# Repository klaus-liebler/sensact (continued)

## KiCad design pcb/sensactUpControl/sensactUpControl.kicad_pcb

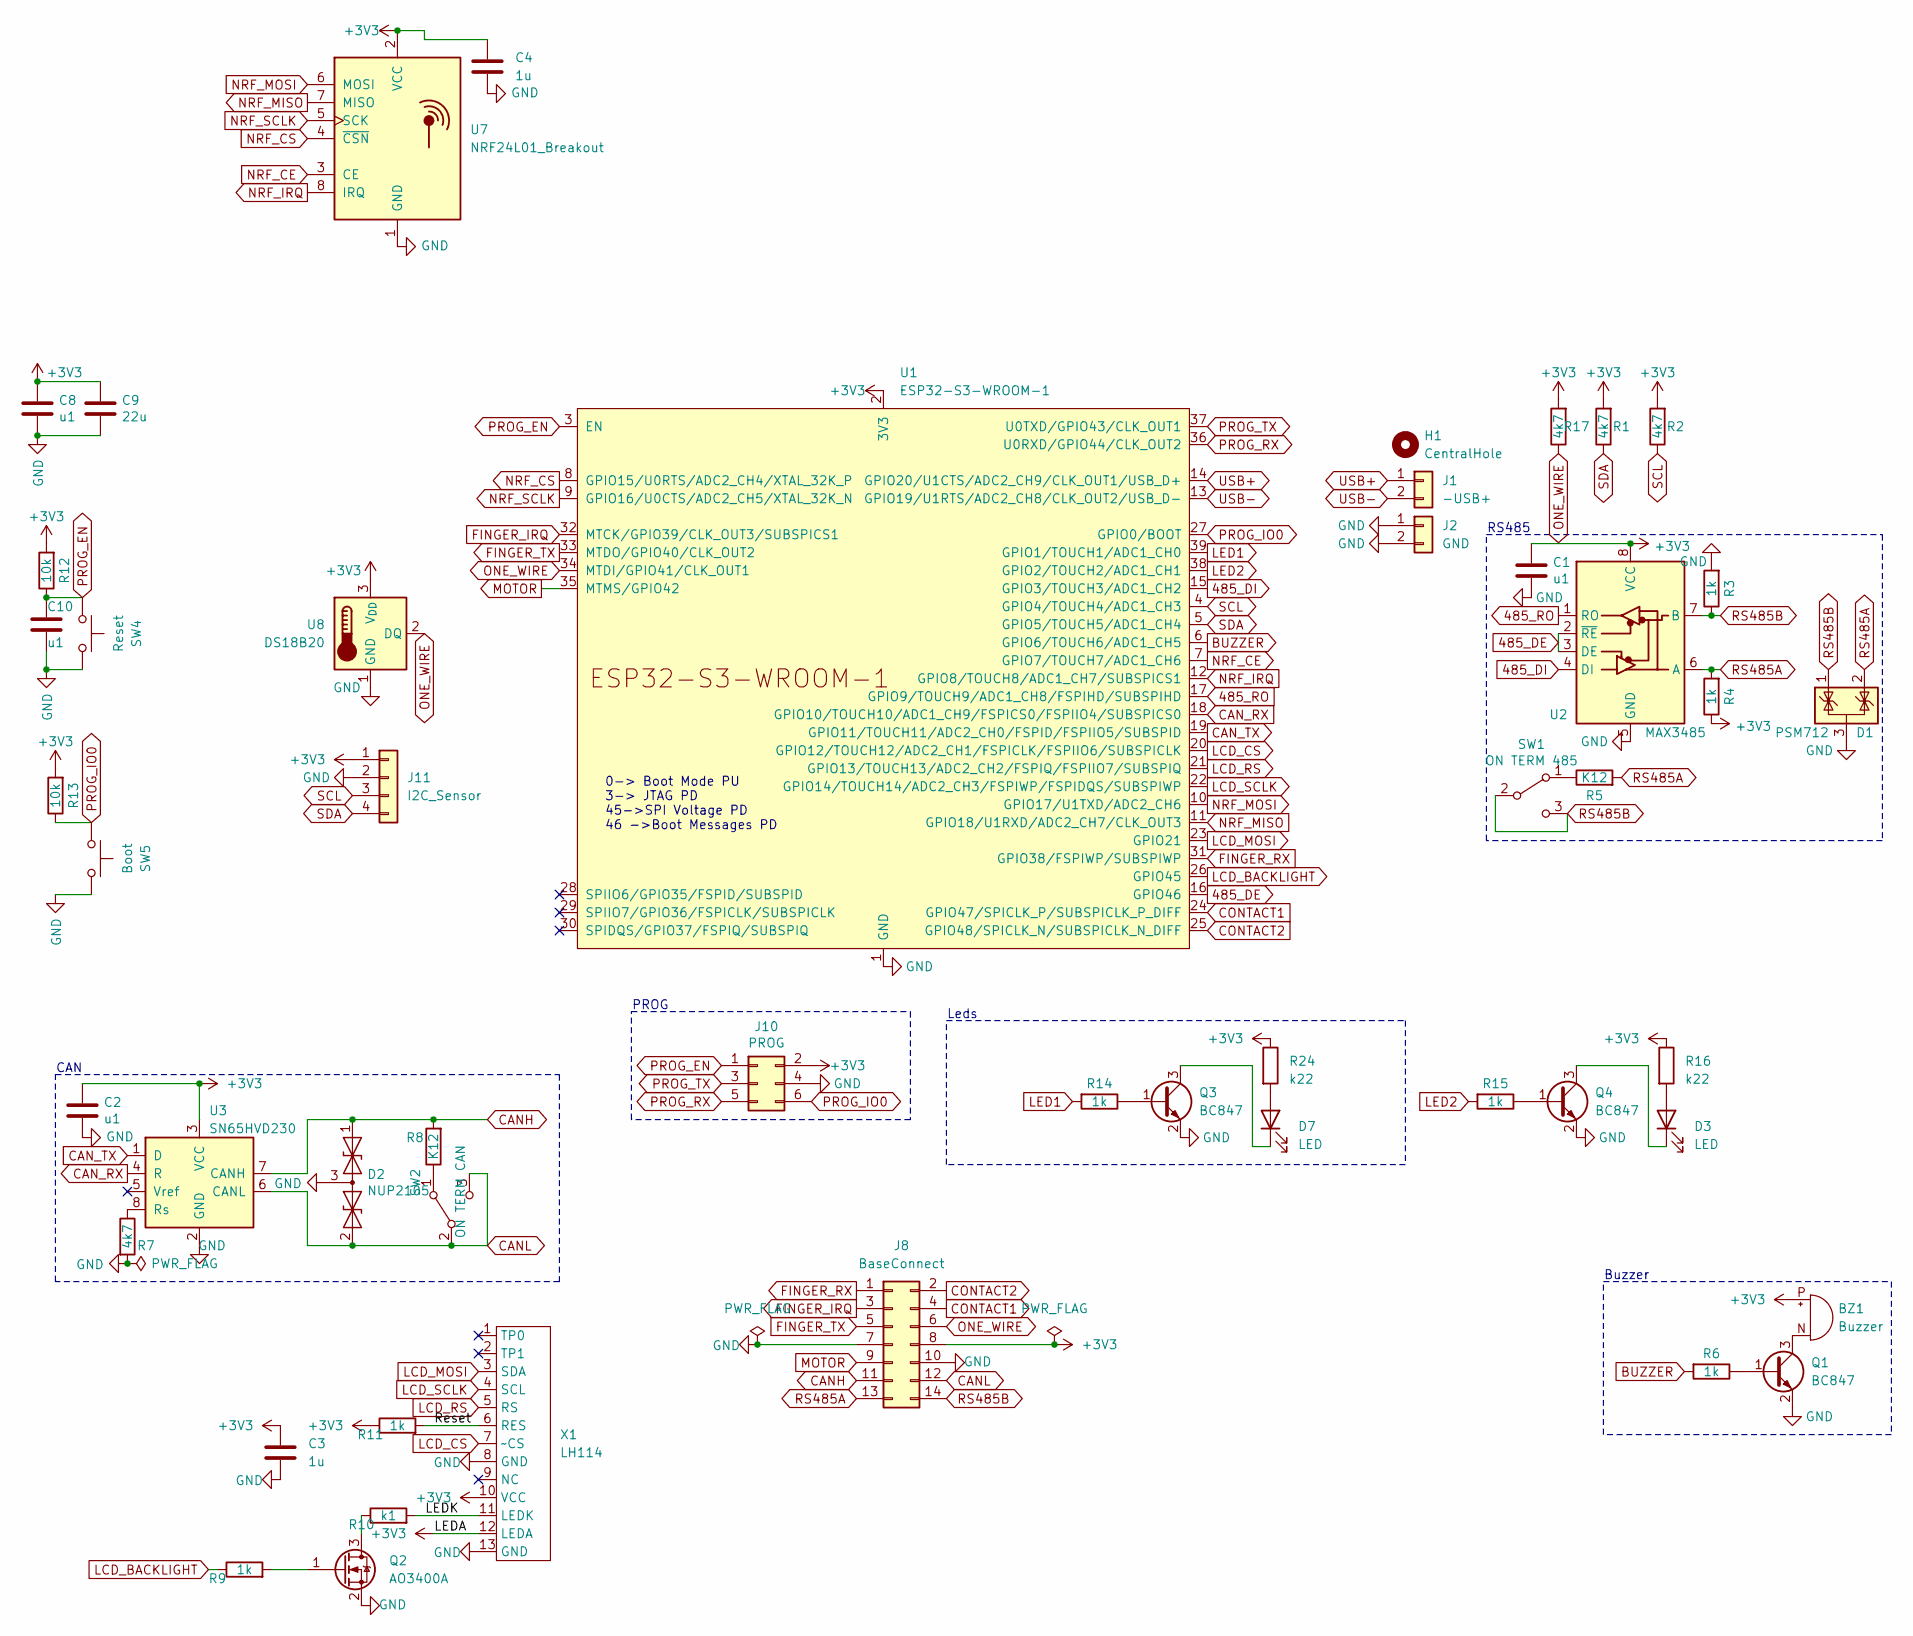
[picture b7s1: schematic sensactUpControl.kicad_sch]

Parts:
BZ1: Buzzer; XDCR_CMT-7525-80-SMT-TR_handsolder
C1, C2, C8, C10: u1; C_0805_2012Metric_Pad1.18x1.45mm_HandSolder
C3, C4: 1u; C_0805_2012Metric_Pad1.18x1.45mm_HandSolder
C9: 22u; C_0805_2012Metric_Pad1.18x1.45mm_HandSolder
D1: PSM712; SOT-23_Handsoldering
D2: NUP2105; SOT-23_Handsoldering
D3, D7: LED; LED_PLCC_2835_Handsoldering
H1: CentralHole; MountingHole_3.2mm_M3
J1: -USB+; PinHeader_1x02_P2.00mm_Vertical
J2: GND; PinHeader_1x02_P2.00mm_Vertical
J8: BaseConnect; PinHeader_2x07_P2.54mm_Vertical
J10: PROG; IDC_2x03_P1.27mm_Vertical
J11: I2C_Sensor; PinHeader_1x04_P2.54mm_Vertical
Q1, Q3, Q4: BC847; SOT-23_Handsoldering
Q2: AO3400A; SOT-23_Handsoldering
R1, R2, R7, R17: 4k7; R_0805_2012Metric_Pad1.20x1.40mm_HandSolder
R3, R4, R6, R9, R11, R14, R15: 1k; R_0805_2012Metric_Pad1.20x1.40mm_HandSolder
R5, R8: K12; R_1206_3216Metric_Pad1.30x1.75mm_HandSolder
R10: k1; R_0805_2012Metric_Pad1.20x1.40mm_HandSolder
R12, R13: 10k; R_0805_2012Metric_Pad1.20x1.40mm_HandSolder
R16, R24: k22; R_1206_3216Metric_Pad1.30x1.75mm_HandSolder
SW1: ON TERM 485; SW_SPDT_PCM12_handsolder
SW2: ON TERM CAN; SW_SPDT_PCM12_handsolder
SW4: Reset; SW_SPST_TL3342_smaller_handsolder
SW5: Boot; SW_SPST_TL3342_smaller_handsolder
U1: ESP32-S3-WROOM-1; ESP32-S3-WROOM-1_handsolder
U2: MAX3485; SOIC-8_3.9x4.9mm_Pitch1.27mm_handsolder
U3: SN65HVD230; SOIC-8_3.9x4.9mm_Pitch1.27mm_handsolder
U7: NRF24L01_Breakout; nRF24L01_Breakout
U8: DS18B20; TO-92_HandSolder
X1: LH114; FP-114 13pol top only

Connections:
485_DE: U1.16 (GPIO46), U2.2 (~RE), U2.3 (DE)
485_DI: U1.15 (GPIO3/TOUCH3/ADC1_CH2), U2.4 (DI)
485_RO: U1.17 (GPIO9/TOUCH9/ADC1_CH8/FSPIHD/SUBSPIHD), U2.1 (RO)
+3V3: BZ1.P (+), C1.2, C2.1, C3.1, C4.1, C8.1, C9.1, J8.8, J10.2, J11.1, R1.2, R2.2, R4.1, R11.1, R12.2, R13.2, R16.1, R17.2, R24.1, U1.2 (3V3), U2.8 (VCC), U3.3 (VCC), U7.2 (VCC), U8.3 (V_{DD}), X1.10 (VCC), X1.12 (LEDA)
/LEDK: R10.2, X1.11 (LEDK)
/Reset: R11.2, X1.6 (RES)
BUZZER: R6.2, U1.6 (GPIO6/TOUCH6/ADC1_CH5)
CANH: D2.1 (A1), J8.11, R8.2, U3.7 (CANH)
CANL: D2.2 (A2), J8.12, SW2.2 (B), SW2.3 (C), U3.6 (CANL)
CAN_RX: U1.18 (GPIO10/TOUCH10/ADC1_CH9/FSPICS0/FSPIIO4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), U3.4 (R)
CAN_TX: U1.19 (GPIO11/TOUCH11/ADC2_CH0/FSPID/FSPIIO5/S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), U3.1 (D)
CONTACT1: J8.4, U1.24 (GPIO47/SPICLK_P/SUBSPICLK_P_DIFF)
CONTACT2: J8.2, U1.25 (GPIO48/SPICLK_N/SUBSPICLK_N_DIFF)
FINGER_IRQ: J8.3, U1.32 (MTCK/GPIO39/CLK_OUT3/SUBSPICS1)
FINGER_RX: J8.1, U1.31 (GPIO38/FSPIWP/SUBSPIWP)
FINGER_TX: J8.5, U1.33 (MTDO/GPIO40/CLK_OUT2)
GND: C1.1, C2.2, C3.2, C4.2, C8.2, C9.2, C10.2, D1.3 (A), D2.3 (common), J2.1, J2.2, J8.7, J8.10, J10.4, J11.2, Q1.2 (E), Q2.2 (S), Q3.2 (E), Q4.2 (E), R3.2, R7.2, SW4.1, SW5.1, U1.1 (GND), U1.40 (GND), U1.41 (GND), U2.5 (GND), U3.2 (GND), U7.1 (GND), U8.1 (GND), X1.8 (GND), X1.13 (GND)
LCD_BACKLIGHT: R9.1, U1.26 (GPIO45)
LCD_CS: U1.20 (GPIO12/TOUCH12/ADC2_CH1/FSPICLK/FSPIIO6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), X1.7 (~CS)
LCD_MOSI: U1.23 (GPIO21), X1.3 (SDA)
LCD_RS: U1.21 (GPIO13/TOUCH13/ADC2_CH2/FSPIQ/FSPIIO7/S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), X1.5 (RS)
LCD_SCLK: U1.22 (GPIO14/TOUCH14/ADC2_CH3/FSPIWP/FSPIDQS/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), X1.4 (SCL)
LED1: R14.2, U1.39 (GPIO1/TOUCH1/ADC1_CH0)
LED2: R15.2, U1.38 (GPIO2/TOUCH2/ADC1_CH1)
MOTOR: J8.9, U1.35 (MTMS/GPIO42)
NRF_CE: U1.7 (GPIO7/TOUCH7/ADC1_CH6), U7.3 (CE)
NRF_CS: U1.8 (GPIO15/U0RTS/ADC2_CH4/XTAL_32K_P), U7.4 (~CSN)
NRF_IRQ: U1.12 (GPIO8/TOUCH8/ADC1_CH7/SUBSPICS1), U7.8 (IRQ)
NRF_MISO: U1.11 (GPIO18/U1RXD/ADC2_CH7/CLK_OUT3), U7.7 (MISO)
NRF_MOSI: U1.10 (GPIO17/U1TXD/ADC2_CH6), U7.6 (MOSI)
NRF_SCLK: U1.9 (GPIO16/U0CTS/ADC2_CH5/XTAL_32K_N), U7.5 (SCK)
unnamed: BZ1.N (-), Q1.3 (C)
unnamed: D3.2 (A), R16.2
unnamed: D3.1 (K), Q4.3 (C)
unnamed: D7.2 (A), R24.2
unnamed: D7.1 (K), Q3.3 (C)
unnamed: Q1.1 (B), R6.1
unnamed: Q2.3 (D), R10.1
unnamed: Q2.1 (G), R9.2
unnamed: Q3.1 (B), R14.1
unnamed: Q4.1 (B), R15.1
unnamed: R5.1, SW1.1 (A)
unnamed: R8.1, SW2.1 (A)
unnamed: R7.1, U3.8 (Rs)
ONE_WIRE: J8.6, R17.1, U1.34 (MTDI/GPIO41/CLK_OUT1), U8.2 (DQ)
PROG_EN: C10.1, J10.1, R12.1, SW4.2, U1.3 (EN)
PROG_IO0: J10.6, R13.1, SW5.2, U1.27 (GPIO0/BOOT)
PROG_RX: J10.5, U1.36 (U0RXD/GPIO44/CLK_OUT2)
PROG_TX: J10.3, U1.37 (U0TXD/GPIO43/CLK_OUT1)
RS485A: D1.2 (K), J8.13, R4.2, R5.2, U2.6 (A)
RS485B: D1.1 (K), J8.14, R3.1, SW1.2 (B), SW1.3 (C), U2.7 (B)
SCL: J11.3, R2.1, U1.4 (GPIO4/TOUCH4/ADC1_CH3)
SDA: J11.4, R1.1, U1.5 (GPIO5/TOUCH5/ADC1_CH4)
USB+: J1.1, U1.14 (GPIO20/U1CTS/ADC2_CH9/CLK_OUT1/USB_D+)
USB-: J1.2, U1.13 (GPIO19/U1RTS/ADC2_CH8/CLK_OUT2/USB_D-)

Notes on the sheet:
Leds
Buzzer
CAN
0-> Boot Mode PU 3-> JTAG PD 45->SPI Voltage PD 46 ->Boot Messages PD
RS485
PROG

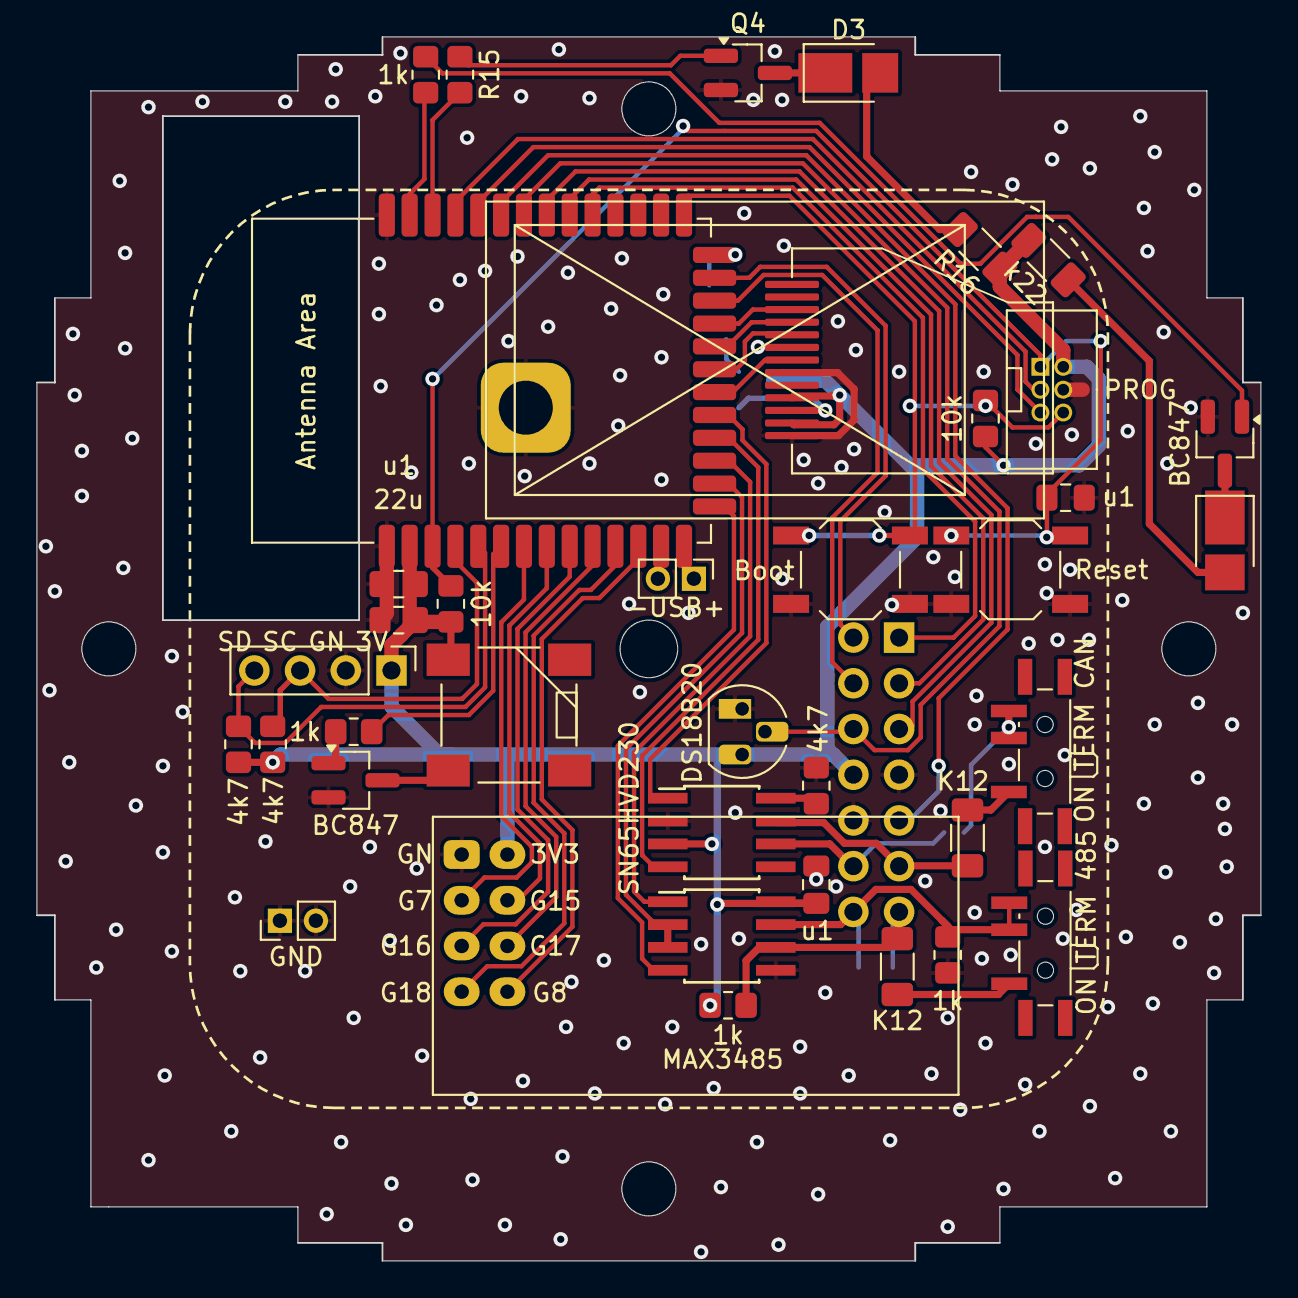
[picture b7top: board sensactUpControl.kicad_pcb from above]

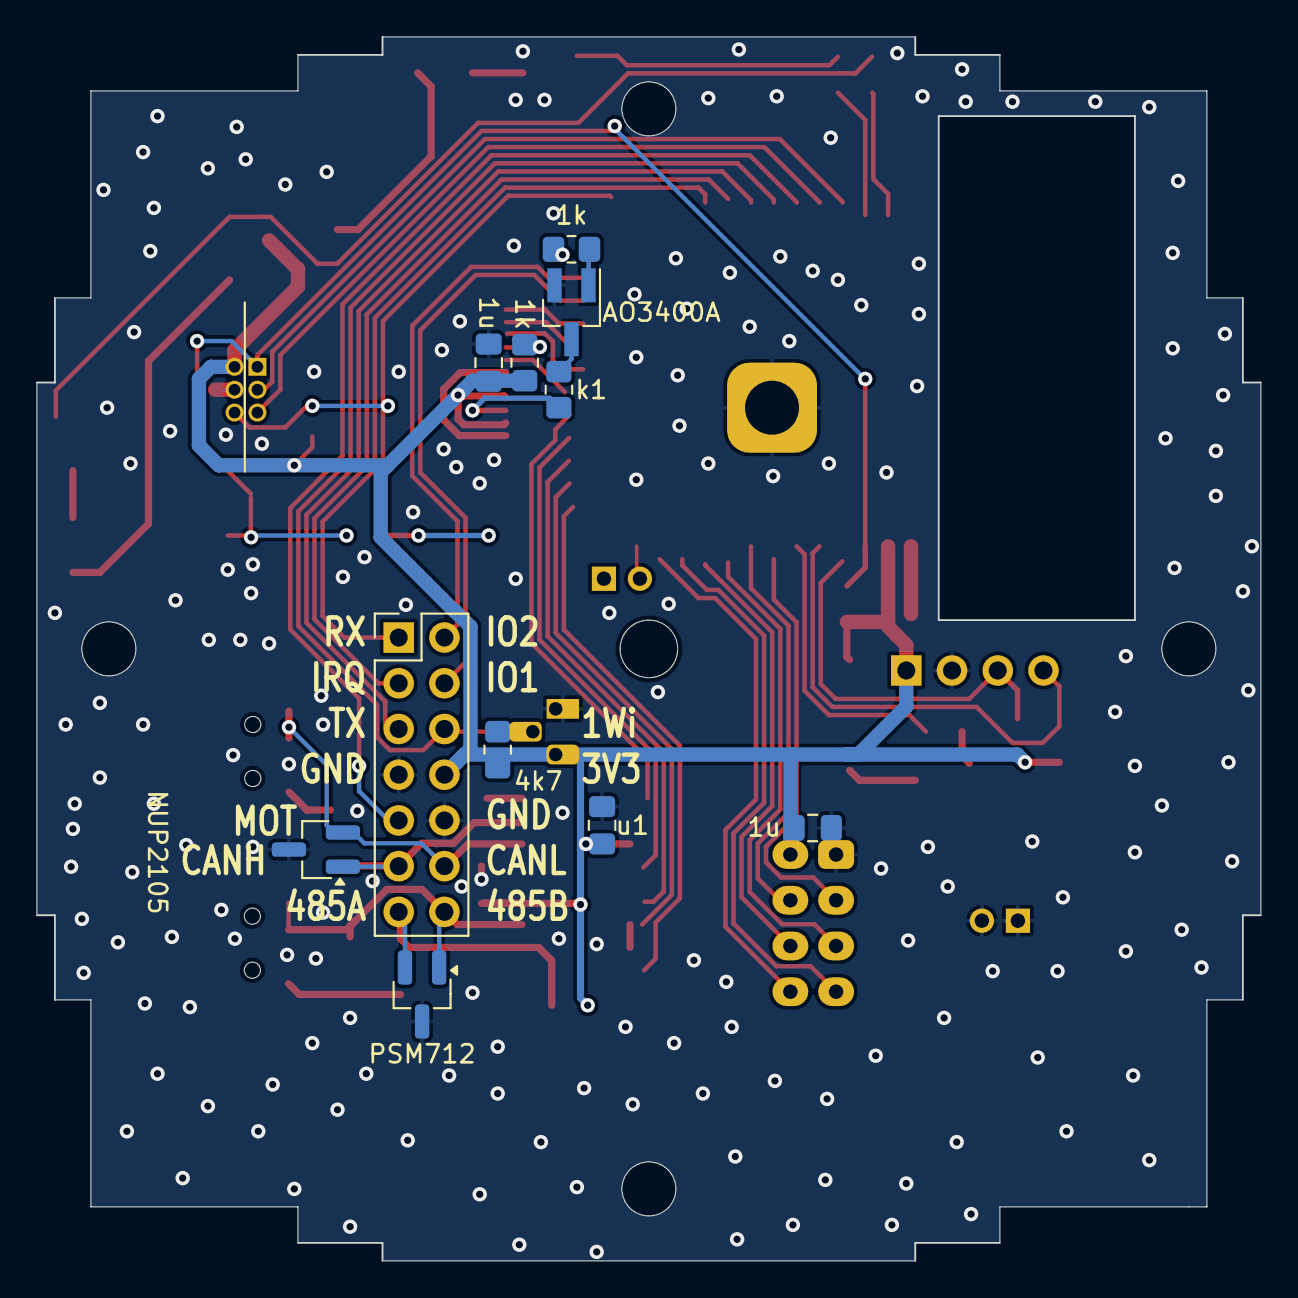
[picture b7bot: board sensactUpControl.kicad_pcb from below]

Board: 2 copper layers, 68.0 x 68.0 mm, 50 parts (11 on the bottom side), 55 nets.

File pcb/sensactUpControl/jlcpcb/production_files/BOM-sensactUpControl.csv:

Comment,Designator,Footprint,LCSC
1k,R3,R_0805_2012Metric_Pad1.20x1.40mm_HandSolder,
MAX3485,U2,SOIC-8_3.9x4.9mm_Pitch1.27mm_handsolder,
4k7,R1,R_0805_2012Metric_Pad1.20x1.40mm_HandSolder,
I2C_Sensor,J11,PinHeader_1x04_P2.54mm_Vertical,
K12,R8,R_1206_3216Metric_Pad1.30x1.75mm_HandSolder,
K12,R5,R_1206_3216Metric_Pad1.30x1.75mm_HandSolder,
22u,C9,C_0805_2012Metric_Pad1.18x1.45mm_HandSolder,
Buzzer,BZ1,XDCR_CMT-7525-80-SMT-TR_handsolder,
BC847,Q1,SOT-23_Handsoldering,
1k,R14,R_0805_2012Metric_Pad1.20x1.40mm_HandSolder,
NRF24L01_Breakout,U7,nRF24L01_Breakout,
10k,R12,R_0805_2012Metric_Pad1.20x1.40mm_HandSolder,
ON TERM CAN,SW2,SW_SPDT_PCM12_handsolder,
4k7,R7,R_0805_2012Metric_Pad1.20x1.40mm_HandSolder,
Boot,SW5,SW_SPST_TL3342_smaller_handsolder,
u1,C1,C_0805_2012Metric_Pad1.18x1.45mm_HandSolder,
GND,J2,PinHeader_1x02_P2.00mm_Vertical,
4k7,R2,R_0805_2012Metric_Pad1.20x1.40mm_HandSolder,
LED,D7,LED_PLCC_2835_Handsoldering,
ESP32-S3-WROOM-1,U1,ESP32-WROOM-32_HANDSOLDER,
CentralHole,H1,MountingHole_3.2mm_M3,
-USB+,J1,PinHeader_1x02_P2.00mm_Vertical,
DS18B20,U8,TO-92_HandSolder,
1k,R4,R_0805_2012Metric_Pad1.20x1.40mm_HandSolder,
LH114,X1,FP-114 13pol top only,
PROG,J10,IDC_2x03_P1.27mm_Vertical,
k22,R24,R_1206_3216Metric_Pad1.30x1.75mm_HandSolder,
Reset,SW4,SW_SPST_TL3342_smaller_handsolder,
u1,C10,C_0805_2012Metric_Pad1.18x1.45mm_HandSolder,
SN65HVD230,U3,SOIC-8_3.9x4.9mm_Pitch1.27mm_handsolder,
1k,R6,R_0805_2012Metric_Pad1.20x1.40mm_HandSolder,
10k,R13,R_0805_2012Metric_Pad1.20x1.40mm_HandSolder,
u1,C8,C_0805_2012Metric_Pad1.18x1.45mm_HandSolder,
ON TERM 485,SW1,SW_SPDT_PCM12_handsolder,
BC847,Q3,SOT-23_Handsoldering,
PSM712,D1,SOT-23_Handsoldering,
1k,R11,R_0805_2012Metric_Pad1.20x1.40mm_HandSolder,
4k7,R17,R_0805_2012Metric_Pad1.20x1.40mm_HandSolder,
1k,R9,R_0805_2012Metric_Pad1.20x1.40mm_HandSolder,
u1,C2,C_0805_2012Metric_Pad1.18x1.45mm_HandSolder,
BaseConnect,J8,PinHeader_2x07_P2.54mm_Vertical,
NUP2105,D2,SOT-23_Handsoldering,
k1,R10,R_0805_2012Metric_Pad1.20x1.40mm_HandSolder,
1u,C3,C_0805_2012Metric_Pad1.18x1.45mm_HandSolder,
1u,C4,C_0805_2012Metric_Pad1.18x1.45mm_HandSolder,

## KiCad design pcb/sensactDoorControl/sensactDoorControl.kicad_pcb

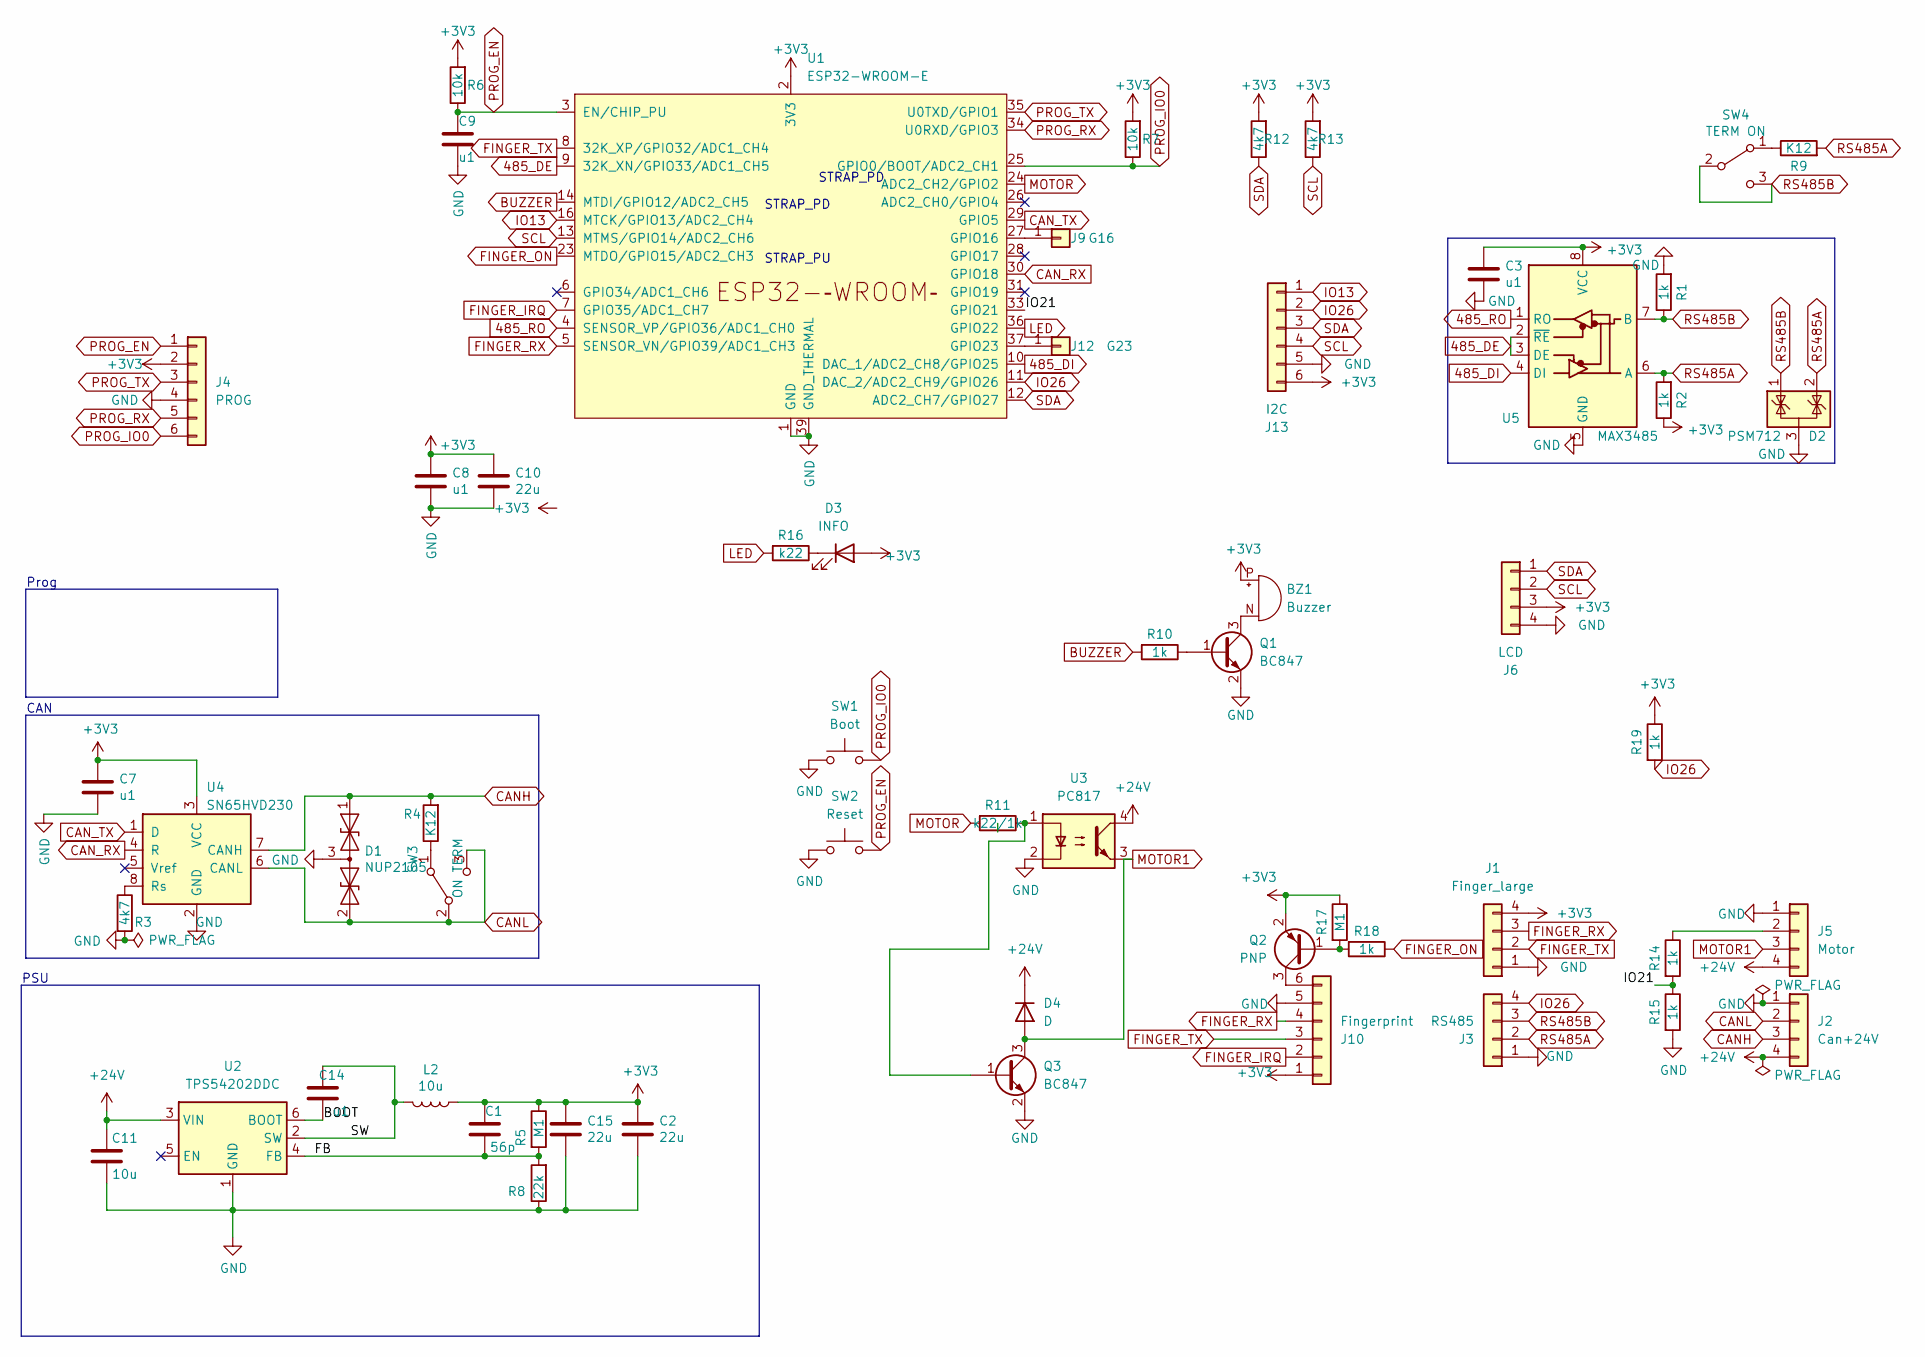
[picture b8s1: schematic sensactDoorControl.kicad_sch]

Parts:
BZ1: Buzzer; XDCR_CMT-7525-80-SMT-TR_handsolder
C1: 56p; C_0805_2012Metric_Pad1.18x1.45mm_HandSolder
C2, C10, C15: 22u; C_0805_2012Metric_Pad1.18x1.45mm_HandSolder
C3, C7, C8, C9, C14: u1; C_0805_2012Metric_Pad1.18x1.45mm_HandSolder
C11: 10u; C_1206_3216Metric_Pad1.33x1.80mm_HandSolder
D1: NUP2105; SOT-23_Handsoldering
D2: PSM712; SOT-23_Handsoldering
D3: INFO; LED_0805_2012Metric_Pad1.15x1.40mm_HandSolder
D4: D; D_SOD-123_handsolder
J1: Finger_large; PhoenixContact_MC_1,5_4-G-3.5_1x04_P3.50mm_Horizontal_small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
J2: Can+24V; PhoenixContact_MC_1,5_4-G-3.5_1x04_P3.50mm_Horizontal_small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
J3: RS485; PhoenixContact_MC_1,5_4-G-3.5_1x04_P3.50mm_Horizontal_small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
J4: PROG; JST_SH_SM06B-SRSS-TB_1x06-1MP_P1.00mm_Horizontal_handsolder
J5: Motor; PhoenixContact_MC_1,5_4-G-3.5_1x04_P3.50mm_Horizontal_small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
J6: LCD; PinSocket_1x04_P2.54mm_Vertical
J9: G16; TestPoint_THTPad_D1.5mm_Drill0.7mm
J10: Fingerprint; JST_SH_SM06B-SRSS-TB_1x06-1MP_P1.00mm_Horizontal_handsolder
J12: G23; TestPoint_THTPad_D1.5mm_Drill0.7mm
J13: I2C; JST_XH_B6B-XH-A_1x06_P2.50mm_Vertical
L2: 10u; L_0630
Q1, Q3: BC847; SOT-23_Handsoldering
Q2: PNP; SOT-23_Handsoldering
R1, R2, R10, R14, R15, R18, R19: 1k; R_0805_2012Metric_Pad1.20x1.40mm_HandSolder
R3, R12, R13: 4k7; R_0805_2012Metric_Pad1.20x1.40mm_HandSolder
R4, R9: K12; R_1206_3216Metric_Pad1.30x1.75mm_HandSolder
R5, R17: M1; R_0805_2012Metric_Pad1.20x1.40mm_HandSolder
R6, R7: 10k; R_0805_2012Metric_Pad1.20x1.40mm_HandSolder
R8: 22k; R_0805_2012Metric_Pad1.20x1.40mm_HandSolder
R11: k22/1k; R_0805_2012Metric_Pad1.20x1.40mm_HandSolder
R16: k22; R_0805_2012Metric_Pad1.20x1.40mm_HandSolder
SW1: Boot; SW_SPST_TL3342_smaller_handsolder
SW2: Reset; SW_SPST_TL3342_smaller_handsolder
SW3: ON TERM; SW_SPDT_PCM12_handsolder
SW4: TERM ON; SW_SPDT_PCM12_handsolder
U1: ESP32-WROOM-E; ESP32-WROOM-32_HANDSOLDER
U2: TPS54202DDC; SOT-23-6_Handsoldering
U3: PC817; mdip_4_handsolder
U4: SN65HVD230; SOIC-8_3.9x4.9mm_Pitch1.27mm_handsolder
U5: MAX3485; SOIC-8_3.9x4.9mm_Pitch1.27mm_handsolder

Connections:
485_DE: U1.9 (32K_XN/GPIO33/ADC1_CH5), U5.2 (~RE), U5.3 (DE)
485_DI: U1.10 (DAC_1/ADC2_CH8/GPIO25), U5.4 (DI)
485_RO: U1.4 (SENSOR_VP/GPIO36/ADC1_CH0), U5.1 (RO)
+3V3: BZ1.P (+), C1.2, C2.1, C3.2, C7.1, C8.1, C10.1, C15.1, D3.2 (A), J1.4, J4.2, J6.3, J10.1, J13.6, L2.1, Q2.2 (E), R2.1, R5.1, R6.2, R7.2, R12.2, R13.2, R17.1, R19.1, U1.2 (3V3), U4.3 (VCC), U5.8 (VCC)
+24V: C11.2, D4.1 (K), J2.4, J5.4, U2.3 (VIN), U3.4
/BOOT: C14.1, U2.6 (BOOT)
/FB: C1.1, R5.2, R8.2, U2.4 (FB)
/IO21: R14.2, R15.1, U1.33 (GPIO21)
/SW: C14.2, L2.2, U2.2 (SW)
BUZZER: R10.2, U1.14 (MTDI/GPIO12/ADC2_CH5)
CANH: D1.1 (A1), J2.3, R4.2, U4.7 (CANH)
CANL: D1.2 (A2), J2.2, SW3.2 (B), SW3.3 (C), U4.6 (CANL)
CAN_RX: U1.30 (GPIO18), U4.4 (R)
CAN_TX: U1.29 (GPIO5), U4.1 (D)
FINGER_IRQ: J10.2, U1.7 (GPIO35/ADC1_CH7)
FINGER_ON: R18.1, U1.23 (MTDO/GPIO15/ADC2_CH3)
FINGER_RX: J1.3, J10.4, U1.5 (SENSOR_VN/GPIO39/ADC1_CH3)
FINGER_TX: J1.2, J10.3, U1.8 (32K_XP/GPIO32/ADC1_CH4)
GND: C2.2, C3.1, C7.2, C8.2, C9.2, C10.2, C11.1, C15.2, D1.3 (common), D2.3 (A), J1.1, J2.1, J3.1, J4.4, J5.1, J6.4, J10.5, J13.5, Q1.2 (E), Q3.2 (E), R1.2, R3.2, R8.1, R15.2, SW1.1, SW2.2, U1.1 (GND), U1.15 (GND), U1.38 (GND), U1.39 (GND_THERMAL), U2.1 (GND), U3.2, U4.2 (GND), U5.5 (GND)
IO13: J13.1, U1.16 (MTCK/GPIO13/ADC2_CH4)
IO26: J3.4, J13.2, R19.2, U1.11 (DAC_2/ADC2_CH9/GPIO26)
LED: R16.2, U1.36 (GPIO22)
MOTOR: R11.2, U1.24 (ADC2_CH2/GPIO2)
MOTOR1: D4.2 (A), J5.3, Q3.3 (C), U3.3
unnamed: BZ1.N (-), Q1.3 (C)
unnamed: D3.1 (K), R16.1
unnamed: J5.2, R14.1
unnamed: J9.1, U1.27 (GPIO16)
unnamed: J10.6, Q2.3 (C)
unnamed: J12.1, U1.37 (GPIO23)
unnamed: Q1.1 (B), R10.1
unnamed: Q2.1 (B), R17.2, R18.2
unnamed: Q3.1 (B), R11.1, U3.1
unnamed: R4.1, SW3.1 (A)
unnamed: R9.1, SW4.1 (A)
unnamed: R3.1, U4.8 (Rs)
PROG_EN: C9.1, J4.1, R6.1, SW2.1, U1.3 (EN/CHIP_PU)
PROG_IO0: J4.6, R7.1, SW1.2, U1.25 (GPIO0/BOOT/ADC2_CH1)
PROG_RX: J4.5, U1.34 (U0RXD/GPIO3)
PROG_TX: J4.3, U1.35 (U0TXD/GPIO1)
RS485A: D2.2 (K), J3.2, R2.2, R9.2, U5.6 (A)
RS485B: D2.1 (K), J3.3, R1.1, SW4.2 (B), SW4.3 (C), U5.7 (B)
SCL: J6.2, J13.4, R13.1, U1.13 (MTMS/GPIO14/ADC2_CH6)
SDA: J6.1, J13.3, R12.1, U1.12 (ADC2_CH7/GPIO27)

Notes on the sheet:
CAN
Prog
STRAP_PU
STRAP_PD
PSU

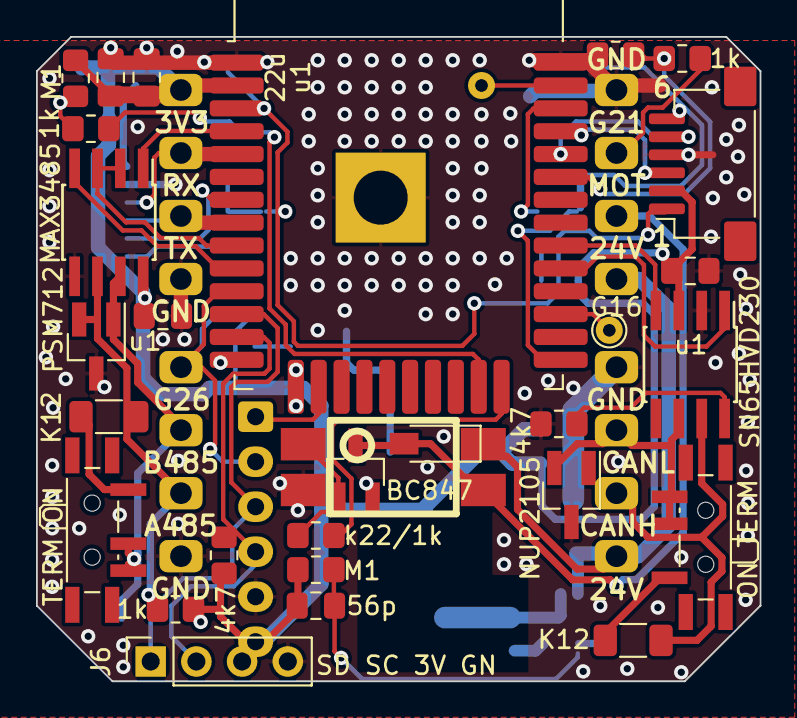
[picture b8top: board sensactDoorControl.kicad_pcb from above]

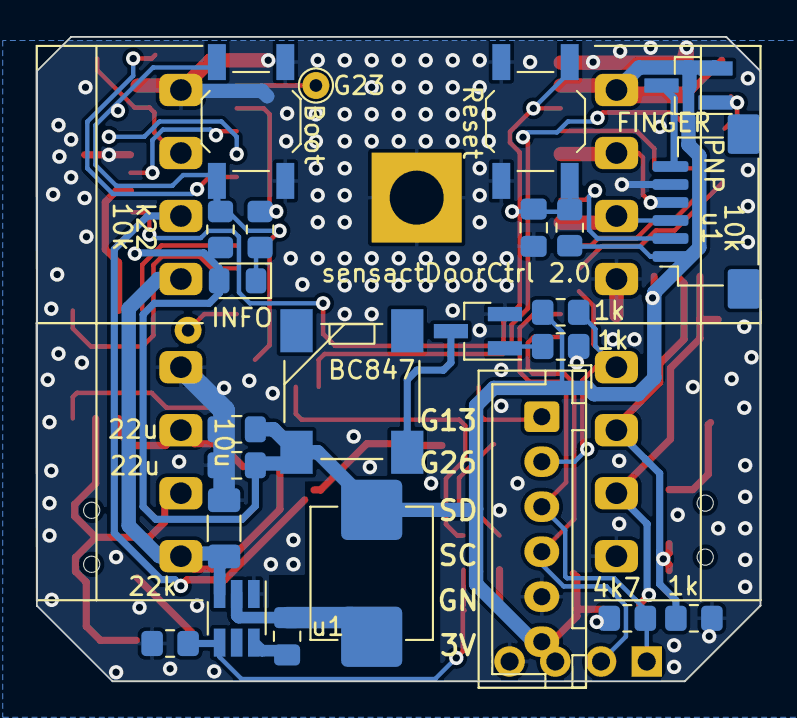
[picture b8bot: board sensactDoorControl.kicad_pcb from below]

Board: 2 copper layers, 40.2 x 35.8 mm, 57 parts (28 on the bottom side), 44 nets.

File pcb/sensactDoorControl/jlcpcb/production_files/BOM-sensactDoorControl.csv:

Comment,Designator,Footprint,LCSC
1k,R14,R_0805_2012Metric_Pad1.20x1.40mm_HandSolder,
4k7,R3,R_0805_2012Metric_Pad1.20x1.40mm_HandSolder,
PSM712,D2,SOT-23_Handsoldering,
PC817,U3,mdip_4_handsolder,
NUP2105,D1,SOT-23_Handsoldering,
k22/1k,R11,R_0805_2012Metric_Pad1.20x1.40mm_HandSolder,
1k,R1,R_0805_2012Metric_Pad1.20x1.40mm_HandSolder,
K12,R4,R_1206_3216Metric_Pad1.30x1.75mm_HandSolder,
56p,C1,C_0805_2012Metric_Pad1.18x1.45mm_HandSolder,
4k7,R13,R_0805_2012Metric_Pad1.20x1.40mm_HandSolder,
u1,C8,C_0805_2012Metric_Pad1.18x1.45mm_HandSolder,
ON TERM,SW3,SW_SPDT_PCM12_handsolder,
ESP32-WROOM-E,U1,ESP32-WROOM-32_HANDSOLDER,
u1,C7,C_0805_2012Metric_Pad1.18x1.45mm_HandSolder,
TERM ON,SW4,SW_SPDT_PCM12_handsolder,
SN65HVD230,U4,SOIC-8_3.9x4.9mm_Pitch1.27mm_handsolder,
K12,R9,R_1206_3216Metric_Pad1.30x1.75mm_HandSolder,
u1,C3,C_0805_2012Metric_Pad1.18x1.45mm_HandSolder,
G16,J9,TestPoint_THTPad_D1.5mm_Drill0.7mm,
G23,J12,TestPoint_THTPad_D1.5mm_Drill0.7mm,
1k,R2,R_0805_2012Metric_Pad1.20x1.40mm_HandSolder,
22u,C10,C_0805_2012Metric_Pad1.18x1.45mm_HandSolder,
M1,R5,R_0805_2012Metric_Pad1.20x1.40mm_HandSolder,
1k,R15,R_0805_2012Metric_Pad1.20x1.40mm_HandSolder,
4k7,R12,R_0805_2012Metric_Pad1.20x1.40mm_HandSolder,
MAX3485,U5,SOIC-8_3.9x4.9mm_Pitch1.27mm_handsolder,
10u,C11,C_1206_3216Metric_Pad1.33x1.80mm_HandSolder,
10u,L2,L_0630,
Reset,SW2,SW_SPST_TL3342_smaller_handsolder,
1k,R10,R_0805_2012Metric_Pad1.20x1.40mm_HandSolder,
u1,C14,C_0805_2012Metric_Pad1.18x1.45mm_HandSolder,
I2C,J13,JST_XH_B6B-XH-A_1x06_P2.50mm_Vertical,
22k,R8,R_0805_2012Metric_Pad1.20x1.40mm_HandSolder,
Fingerprint,J10,JST_SH_SM06B-SRSS-TB_1x06-1MP_P1.00mm_Horizontal_handsolder,
Can+24V,J2,"PhoenixContact_MC_1,5_4-G-3.5_1x04_P3.50mm_Horizontal_smallerCourtyard",
Boot,SW1,SW_SPST_TL3342_smaller_handsolder,
10k,R7,R_0805_2012Metric_Pad1.20x1.40mm_HandSolder,
u1,C9,C_0805_2012Metric_Pad1.18x1.45mm_HandSolder,
INFO,D3,LED_0805_2012Metric_Pad1.15x1.40mm_HandSolder,
RS485,J3,"PhoenixContact_MC_1,5_4-G-3.5_1x04_P3.50mm_Horizontal_smallerCourtyard",
22u,C15,C_0805_2012Metric_Pad1.18x1.45mm_HandSolder,
Finger_large,J1,"PhoenixContact_MC_1,5_4-G-3.5_1x04_P3.50mm_Horizontal_smallerCourtyard",
10k,R6,R_0805_2012Metric_Pad1.20x1.40mm_HandSolder,
TPS54202DDC,U2,SOT-23-6_Handsoldering,
Motor,J5,"PhoenixContact_MC_1,5_4-G-3.5_1x04_P3.50mm_Horizontal_smallerCourtyard",
PROG,J4,JST_SH_SM06B-SRSS-TB_1x06-1MP_P1.00mm_Horizontal_handsolder,
Buzzer,BZ1,XDCR_CMT-7525-80-SMT-TR_handsolder,
BC847,Q1,SOT-23_Handsoldering,
22u,C2,C_0805_2012Metric_Pad1.18x1.45mm_HandSolder,
1k,R18,R_0805_2012Metric_Pad1.20x1.40mm_HandSolder,
M1,R17,R_0805_2012Metric_Pad1.20x1.40mm_HandSolder,
PNP,Q2,SOT-23_Handsoldering,
k22,R16,R_0805_2012Metric_Pad1.20x1.40mm_HandSolder,
D,D4,D_SOD-123_handsolder,
BC847,Q3,SOT-23_Handsoldering,
LCD,J6,PinHeader_1x04_P2.54mm_Vertical,
1k,R19,R_0805_2012Metric_Pad1.20x1.40mm_HandSolder,

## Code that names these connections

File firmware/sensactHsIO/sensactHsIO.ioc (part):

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Mcu.Name=STM32F072R(8-B)Tx
Mcu.Package=LQFP64
Mcu.UserName=STM32F072RBTx
PA10.Mode=Asynchronous
PA10.Signal=USART1_RX
PA11.Mode=Device
PA11.Signal=USB_DM
PA12.Mode=Device
PA12.Signal=USB_DP
PA13.Mode=Serial_Wire
PA13.Signal=SYS_SWDIO
PA14.Mode=Serial_Wire
PA14.Signal=SYS_SWCLK
PA15.GPIOParameters=GPIO_Label
PA15.GPIO_Label=INT2
PA15.Signal=GPIO_Input
PA2.Mode=Asynchronous
PA2.Signal=USART2_TX
PA3.Mode=Asynchronous
PA3.Signal=USART2_RX
PA6.GPIOParameters=GPIO_Label
PA6.GPIO_Label=I06
PA6.Signal=GPIO_Input
PA7.GPIOParameters=GPIO_Label
PA7.GPIO_Label=I07
PA7.Signal=GPIO_Input
PA8.GPIOParameters=GPIO_Label
PA8.GPIO_Label=VBUS
PA8.Signal=GPIO_Input
PA9.Mode=Asynchronous
PA9.Signal=USART1_TX
PB0.GPIOParameters=GPIO_Label
PB0.GPIO_Label=I02
PB0.Signal=GPIO_Input
PB1.GPIOParameters=GPIO_Label
PB1.GPIO_Label=I03
PB1.Signal=GPIO_Input
PB10.GPIOParameters=GPIO_Label
PB10.GPIO_Label=SCL
PB10.Mode=I2C
PB10.Signal=I2C2_SCL
PB11.GPIOParameters=GPIO_Label
PB11.GPIO_Label=SDA
PB11.Mode=I2C
PB11.Signal=I2C2_SDA
PB12.GPIOParameters=GPIO_Label
PB12.GPIO_Label=SPIB_CS
PB12.Signal=GPIO_Output
PB13.GPIOParameters=GPIO_Label
PB13.GPIO_Label=SPIB_CLK
PB13.Mode=Full_Duplex_Master
PB13.Signal=SPI2_SCK
PB14.GPIOParameters=GPIO_Label
PB14.GPIO_Label=SPIB_MISO
PB14.Mode=Full_Duplex_Master
PB14.Signal=SPI2_MISO
PB15.GPIOParameters=GPIO_Label
PB15.GPIO_Label=SPIB_MOSI
PB15.Mode=Full_Duplex_Master
PB15.Signal=SPI2_MOSI
PB2.GPIOParameters=GPIO_Label
PB2.GPIO_Label=ROTS
PB2.Signal=GPIO_Input
PB3.GPIOParameters=GPIO_Label
PB3.GPIO_Label=LCD_CLK
PB3.Mode=TX_Only_Simplex_Unidirect_Master
PB3.Signal=SPI1_SCK
PB4.GPIOParameters=GPIO_Label
PB4.GPIO_Label=I12
PB4.Signal=GPIO_Input
PB5.GPIOParameters=GPIO_Label
PB5.GPIO_Label=LCD_MOSI
PB5.Mode=TX_Only_Simplex_Unidirect_Master
PB5.Signal=SPI1_MOSI
PB6.GPIOParameters=GPIO_Label
PB6.GPIO_Label=LCD_RS
PB6.Signal=GPIO_Output
PB7.GPIOParameters=GPIO_Label
PB7.GPIO_Label=LCD_BL
PB7.Signal=GPIO_Output
PB8.Mode=Master
PB8.Signal=CAN_RX
PB9.Mode=Master
PB9.Signal=CAN_TX
PC0.GPIOParameters=GPIO_Label
PC0.GPIO_Label=I10
PC0.Signal=GPIO_Input
PC1.GPIOParameters=GPIO_Label
PC1.GPIO_Label=I11
PC1.Signal=GPIO_Input
PC12.GPIOParameters=GPIO_Label
PC12.GPIO_Label=LCD_RST
PC12.Signal=GPIO_Output
PC13.GPIOParameters=GPIO_Label
PC13.GPIO_Label=I13
PC13.Signal=GPIO_Input
PC14-OSC32_IN.GPIOParameters=GPIO_Label
PC14-OSC32_IN.GPIO_Label=I14
PC14-OSC32_IN.Signal=GPIO_Input
PC15-OSC32_OUT.GPIOParameters=GPIO_Label
PC15-OSC32_OUT.GPIO_Label=I15
PC15-OSC32_OUT.Signal=GPIO_Input
PC2.GPIOParameters=GPIO_Label
PC2.GPIO_Label=I04
PC2.Signal=GPIO_Input
PC3.GPIOParameters=GPIO_Label
PC3.GPIO_Label=I05
PC3.Signal=GPIO_Input
PC4.GPIOParameters=GPIO_Label
PC4.GPIO_Label=I00
PC4.Signal=GPIO_Input
PC5.GPIOParameters=GPIO_Label
PC5.GPIO_Label=I01
PC5.Signal=GPIO_Input
PC6.GPIOParameters=GPIO_Label
PC6.GPIO_Label=ROTB
PC6.Signal=S_TIM3_CH1
PC7.GPIOParameters=GPIO_Label
PC7.GPIO_Label=ROTA
PC7.Signal=S_TIM3_CH2
PC8.GPIOParameters=GPIO_Label
PC8.GPIO_Label=INT0
PC8.Signal=GPIO_Input
PC9.GPIOParameters=GPIO_Label
PC9.GPIO_Label=INT1
PC9.Signal=GPIO_Input
PD2.GPIOParameters=GPIO_Label
PD2.GPIO_Label=LCD_CS
PD2.Signal=GPIO_Output
PF0-OSC_IN.GPIOParameters=GPIO_Label
PF0-OSC_IN.GPIO_Label=I08
PF0-OSC_IN.Signal=GPIO_Input
PF1-OSC_OUT.GPIOParameters=GPIO_Label
PF1-OSC_OUT.GPIO_Label=I09
PF1-OSC_OUT.Signal=GPIO_Input
RCC.SYSCLKFreq_VALUE=48000000
RCC.SYSCLKSource=RCC_SYSCLKSOURCE_HSI48
board=custom
